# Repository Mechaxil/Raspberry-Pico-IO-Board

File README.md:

# Mechaxil Pico IO Board - [Documentation website](https://docs.mechaxil.com/docs/products/pico-io-board)

A clean, minimal Raspberry Pi Pico-compatible breakout board designed for easy access to all GPIO pins.

## Overview

The Mechaxil Pico IO Board expands the Raspberry Pi Pico pins so it's easier to use for prototyping.

Designed with usability, readability, and clean aesthetics in mind.

Perfect for prototyping, education, embedded development, and quick testing setups.

This board is available for purchase via the Mechaxil webshop:
[Mechaxil Webshop](https://mechaxil.com/products/pico-io-board)

## Features

- Full GPIO breakout  
- Clearly labeled pinout on silkscreen  
- Single-row female header  
- Dual-row male headers  
- Clean minimal design  

## Use Cases

- Rapid prototyping  
- Educational electronics kits  
- Embedded system development  
- DIY projects  

## Hardware

- Compatible with Raspberry Pi Pico and Pico-compatible boards  
- Standard 2.54 mm header spacing  
- Compact form factor  

## OSHW & License

As of 2026 May 8th this project was certified by OSHWA

This project is licensed under the CERN Open Hardware Licence Version 2 - Weakly Reciprocal (CERN-OHL-W).

You are free to use, modify, manufacture, and sell.

Condition:
- Any modifications to the design must also be shared under the same license  

> [!IMPORTANT]
>
> ## Trademark & Branding Notice
>
> "Mechaxil" and the Mechaxil logo are trademarks of Mechaxil (Závoczki Attila e.v.).
> This license does not grant permission to use the Mechaxil name, logo, or branding for commercial or promotional purposes without prior written permission.
>
> If you manufacture, distribute, or sell this design (modified or unmodified):
>
> * You must remove the Mechaxil logo
> * You must remove any "Approved by Mechaxil" markings
> * You must not imply that your product is an official Mechaxil product
> * You must clearly state: "Original design by Mechaxil"
>
> This ensures transparency and avoids confusion between official Mechaxil products and third-party derivatives.

> [!IMPORTANT]
> ## Raspberry Pi Disclaimer
> "Raspberry Pi" is a trademark of the Raspberry Pi Foundation.
> This project is not affiliated with, endorsed by, or sponsored by the Raspberry Pi Foundation or Raspberry Pi Ltd.
> The term is used only for compatibility reference.

## Open Hardware

All design files are provided as schematics, PCB layouts, and production files.

Feel free to build, sell, improve, and share.

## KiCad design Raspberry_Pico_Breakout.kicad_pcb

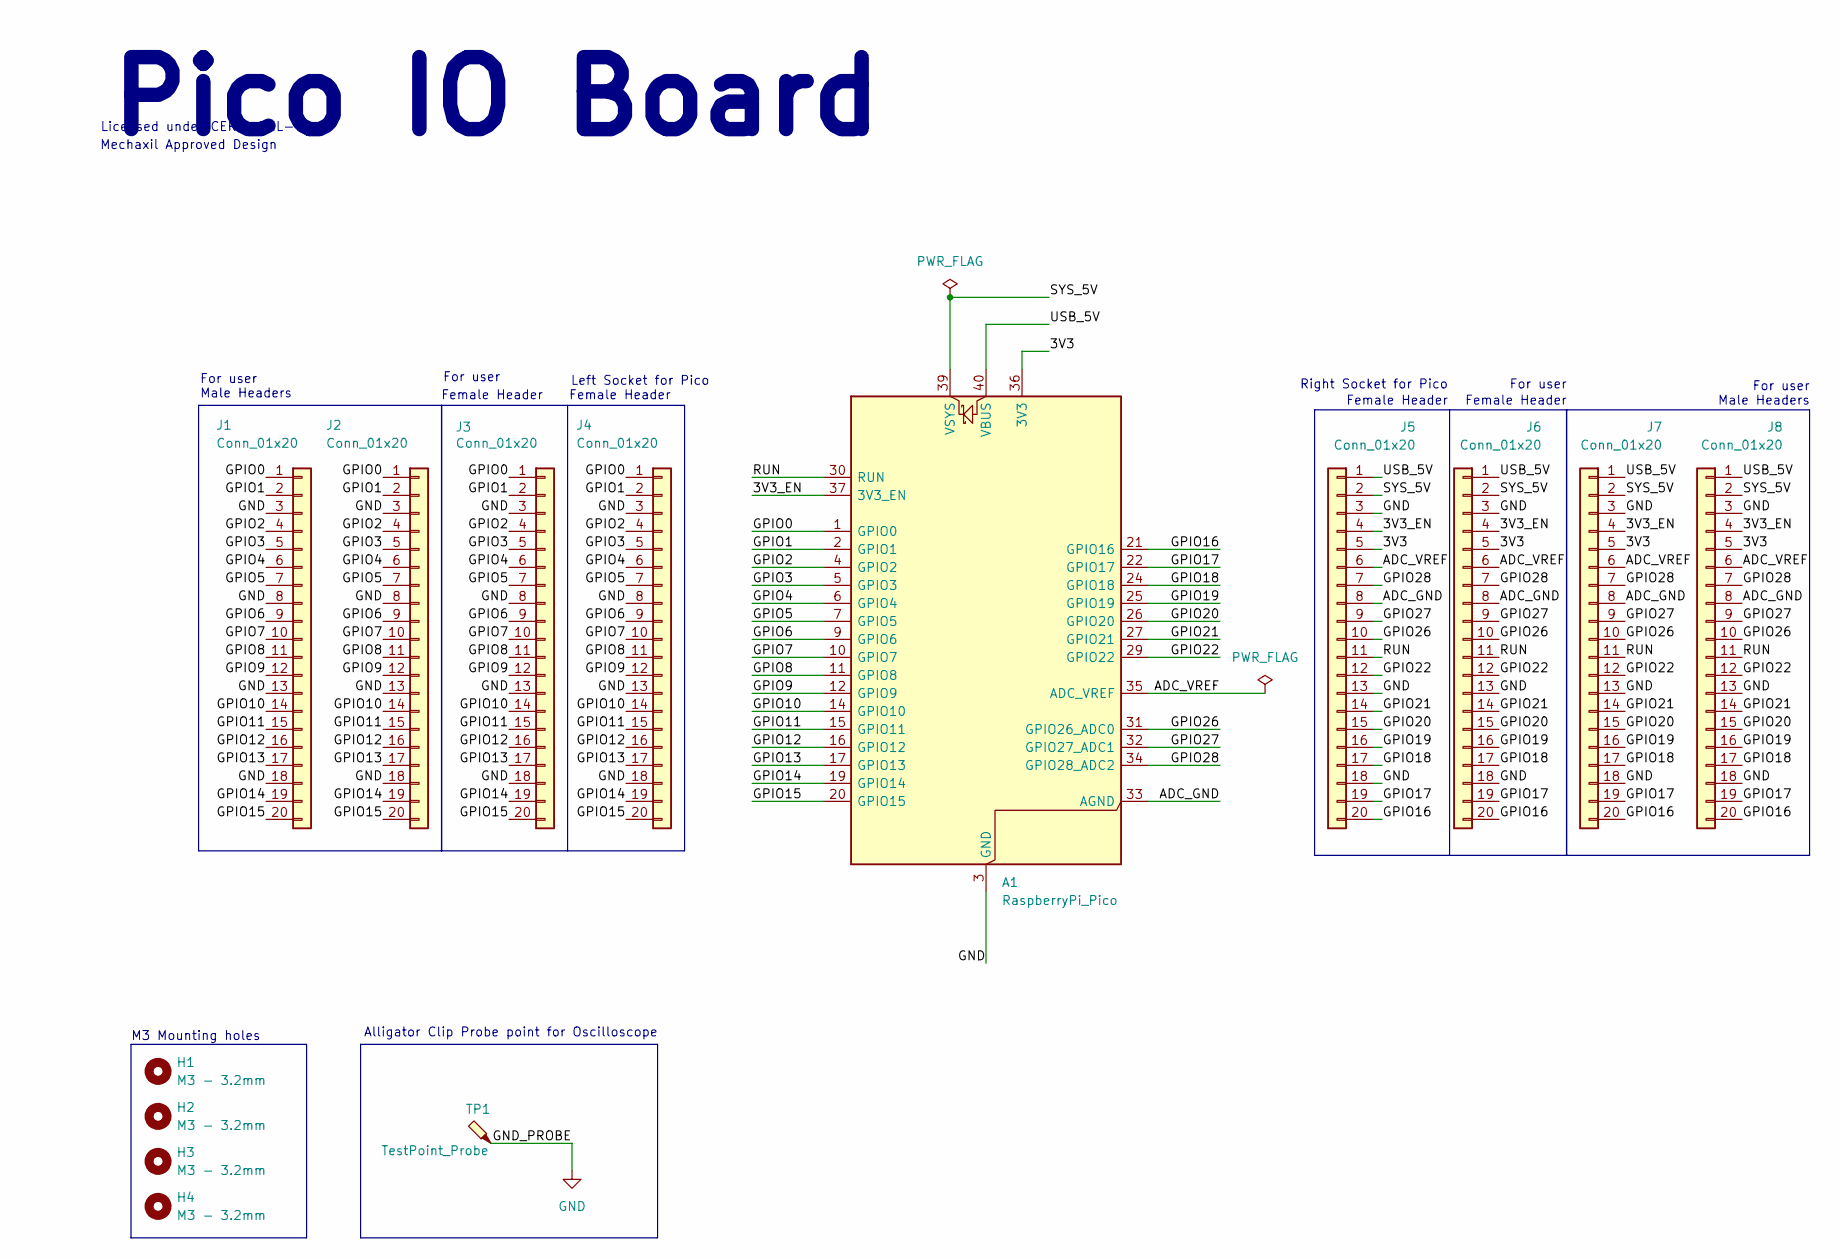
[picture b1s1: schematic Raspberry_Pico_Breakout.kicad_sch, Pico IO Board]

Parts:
A1: RaspberryPi_Pico; RaspberryPi_Pico_Common_Unspecified
H1, H2, H3, H4: M3 - 3.2mm; MountingHole_3.2mm_M3_ISO_4762
J1, J2, J7, J8: Conn_01x20; PinHeader_1x20_P2.54mm_Vertical_NoSilkscreen
J3, J4, J5, J6: Conn_01x20; PinSocket_1x20_P2.54mm_Vertical_NoSilkscreen
TP1: TestPoint_Probe; TestPoint_Loop_D2.50mm_Drill1.0mm_LowProfile

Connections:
/3V3: A1.36 (3V3), J5.5, J6.5, J7.5, J8.5
/3V3_EN: A1.37 (3V3_EN), J5.4, J6.4, J7.4, J8.4
/ADC_GND: A1.33 (AGND), J5.8, J6.8, J7.8, J8.8
/ADC_VREF: A1.35 (ADC_VREF), J5.6, J6.6, J7.6, J8.6
/GPIO0: A1.1 (GPIO0), J1.1, J2.1, J3.1, J4.1
/GPIO1: A1.2 (GPIO1), J1.2, J2.2, J3.2, J4.2
/GPIO2: A1.4 (GPIO2), J1.4, J2.4, J3.4, J4.4
/GPIO3: A1.5 (GPIO3), J1.5, J2.5, J3.5, J4.5
/GPIO4: A1.6 (GPIO4), J1.6, J2.6, J3.6, J4.6
/GPIO5: A1.7 (GPIO5), J1.7, J2.7, J3.7, J4.7
/GPIO6: A1.9 (GPIO6), J1.9, J2.9, J3.9, J4.9
/GPIO7: A1.10 (GPIO7), J1.10, J2.10, J3.10, J4.10
/GPIO8: A1.11 (GPIO8), J1.11, J2.11, J3.11, J4.11
/GPIO9: A1.12 (GPIO9), J1.12, J2.12, J3.12, J4.12
/GPIO10: A1.14 (GPIO10), J1.14, J2.14, J3.14, J4.14
/GPIO11: A1.15 (GPIO11), J1.15, J2.15, J3.15, J4.15
/GPIO12: A1.16 (GPIO12), J1.16, J2.16, J3.16, J4.16
/GPIO13: A1.17 (GPIO13), J1.17, J2.17, J3.17, J4.17
/GPIO14: A1.19 (GPIO14), J1.19, J2.19, J3.19, J4.19
/GPIO15: A1.20 (GPIO15), J1.20, J2.20, J3.20, J4.20
/GPIO16: A1.21 (GPIO16), J5.20, J6.20, J7.20, J8.20
/GPIO17: A1.22 (GPIO17), J5.19, J6.19, J7.19, J8.19
/GPIO18: A1.24 (GPIO18), J5.17, J6.17, J7.17, J8.17
/GPIO19: A1.25 (GPIO19), J5.16, J6.16, J7.16, J8.16
/GPIO20: A1.26 (GPIO20), J5.15, J6.15, J7.15, J8.15
/GPIO21: A1.27 (GPIO21), J5.14, J6.14, J7.14, J8.14
/GPIO22: A1.29 (GPIO22), J5.12, J6.12, J7.12, J8.12
/GPIO26: A1.31 (GPIO26_ADC0), J5.10, J6.10, J7.10, J8.10
/GPIO27: A1.32 (GPIO27_ADC1), J5.9, J6.9, J7.9, J8.9
/GPIO28: A1.34 (GPIO28_ADC2), J5.7, J6.7, J7.7, J8.7
/RUN: A1.30 (RUN), J5.11, J6.11, J7.11, J8.11
/SYS_5V: A1.39 (VSYS), J5.2, J6.2, J7.2, J8.2
/USB_5V: A1.40 (VBUS), J5.1, J6.1, J7.1, J8.1
GND: A1.3 (GND), A1.8 (GND), A1.13 (GND), A1.18 (GND), A1.23 (GND), A1.28 (GND), A1.38 (GND), J1.3, J1.8, J1.13, J1.18, J2.3, J2.8, J2.13, J2.18, J3.3, J3.8, J3.13, J3.18, J4.3, J4.8, J4.13, J4.18, J5.3, J5.13, J5.18, J6.3, J6.13, J6.18, J7.3, J7.13, J7.18, J8.3, J8.13, J8.18, TP1.1 (1_1)

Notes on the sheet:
Licensed under CERN-OHL-W v2
Pico IO Board
Left Socket for Pico
Mechaxil Approved Design
Female Header
Male Headers
For user
M3 Mounting holes
Right Socket for Pico
Alligator Clip Probe point for Oscilloscope

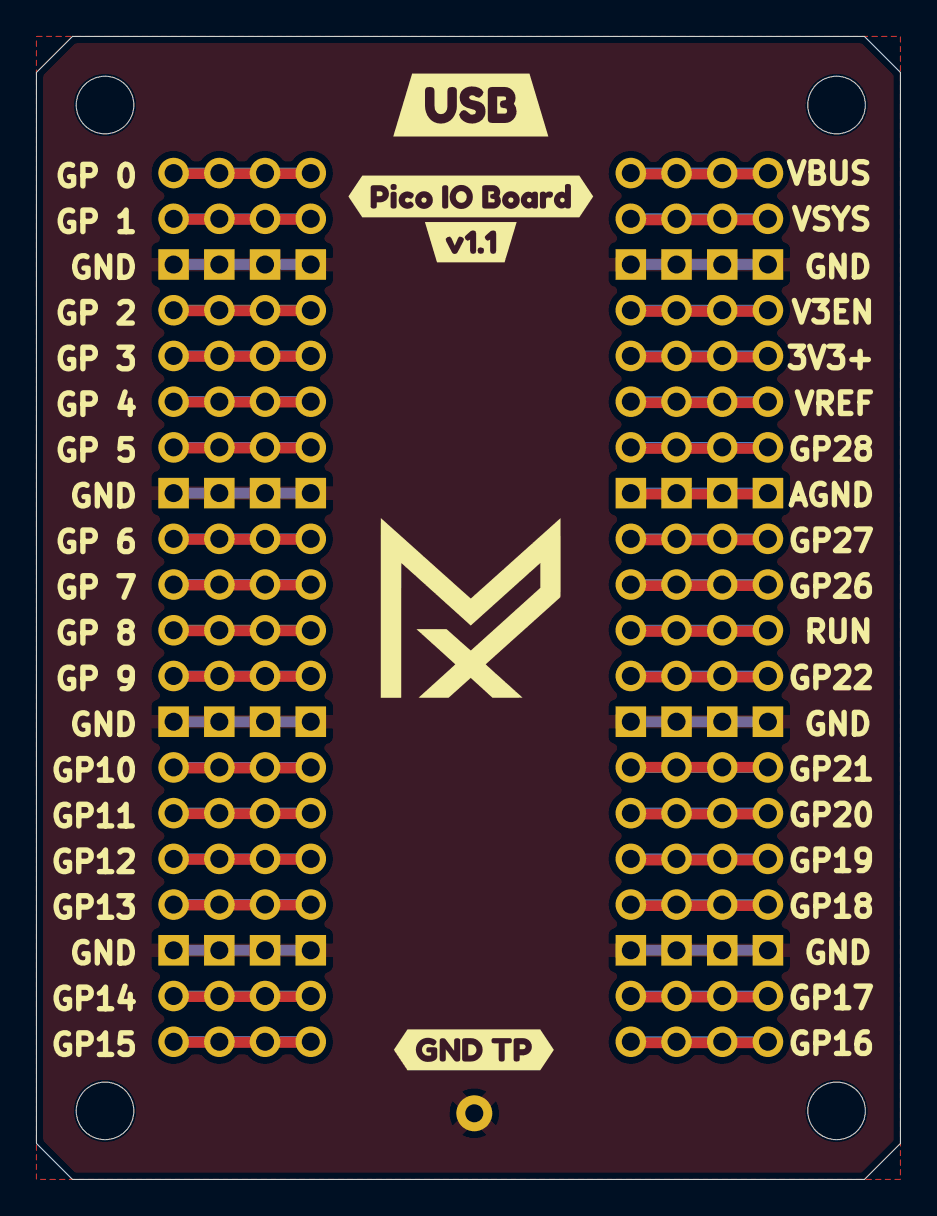
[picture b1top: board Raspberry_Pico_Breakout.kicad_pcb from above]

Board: 2 copper layers, 48.0 x 63.5 mm, 17 parts (0 on the bottom side), 34 nets.

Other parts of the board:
kibuzzard-6A0C12EA: G***; kibuzzard-6A0C12EA
kibuzzard-6A0C1342: G***; kibuzzard-6A0C1342
kibuzzard-694057F1: G***; kibuzzard-694057F1
kibuzzard-6940576A: G***; kibuzzard-6940576A

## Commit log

2026-03-28 fix: license file name
2026-05-01 doc: updated part documentation, schematics readability
2026-05-03 doc: updated on schematic and PCB added license and design text
2026-05-09 major: upgrade to KiCAD 10.0 and OSHW License
2026-05-10 doc: README title and add documentation link
2026-05-18 Doc: update layers and sch, change font to space mono, export step
2026-05-18 fix: remove temp doc
2026-05-19 feat: Probe GND pad for easy oscilloscope attachment

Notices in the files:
Raspberry_Pico_Breakout.kicad_pcb:
Licensed under CERN-OHL-W v2.0
